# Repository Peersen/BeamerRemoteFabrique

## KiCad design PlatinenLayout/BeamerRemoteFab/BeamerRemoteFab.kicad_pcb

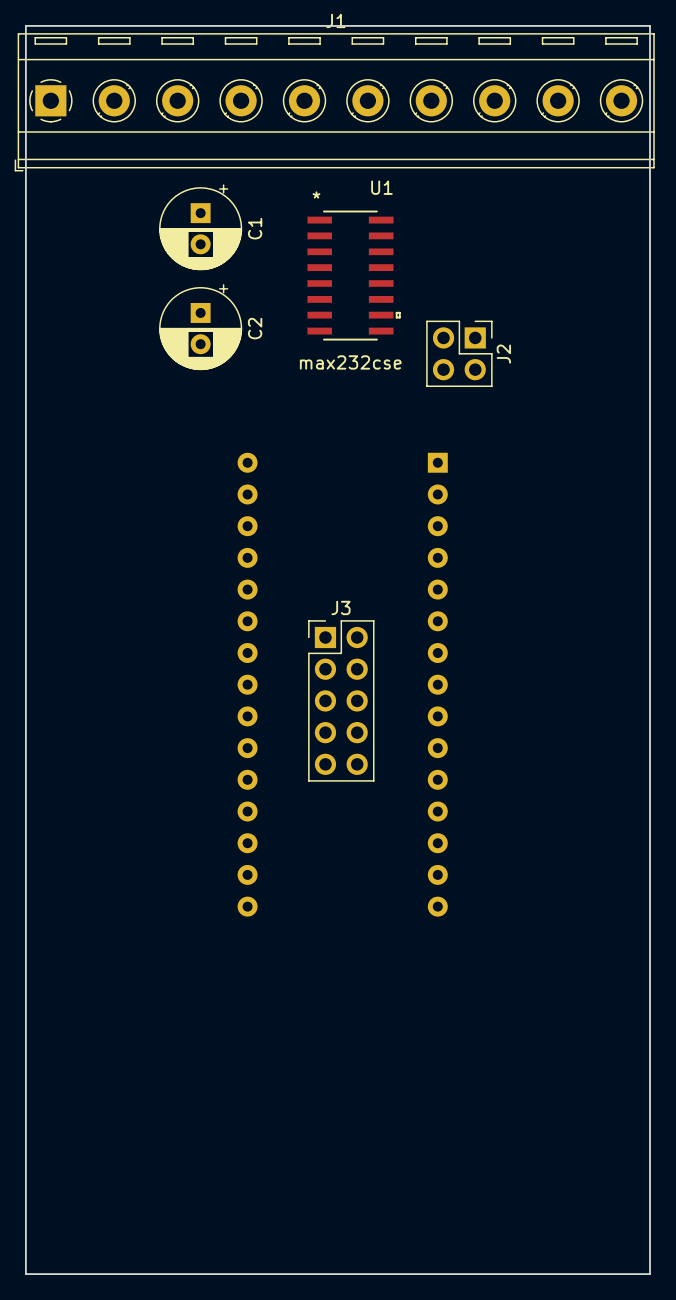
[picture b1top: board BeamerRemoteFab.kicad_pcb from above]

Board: 2 copper layers, 50.0 x 100.0 mm, 7 parts (1 on the bottom side), 12 nets, no tracks yet.

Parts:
A1: Arduino_Nano_v3.x; Arduino_Nano
C1, C2: CP; CP_Radial_D6.3mm_P2.50mm
J1: Conn_01x10; TerminalBlock_RND_205-00295_1x10_P5.08mm_Horizontal
J2: Conn_02x02_Odd_Even; PinHeader_2x02_P2.54mm_Vertical
J3: Conn_02x05_Counter_Clockwise; PinHeader_2x05_P2.54mm_Vertical
U1: max232cse

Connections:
+5V: A1.27, U1.16
GND: A1.4, A1.29, U1.15
unnamed: A1.1, J2.4
unnamed: A1.2, J2.2
unnamed: C1.1, U1.1
unnamed: C1.2, U1.3
unnamed: C2.1, U1.4
unnamed: C2.2, U1.5
unnamed: J1.1, U1.14
unnamed: J1.2, U1.13
unnamed: J2.1, U1.12
unnamed: J2.3, U1.11
